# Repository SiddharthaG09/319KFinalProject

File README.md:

# 319KFinalProject

For our final project, we recreated Space Invaders in C, using a custom-designed PCB and an MSPM0G3507 microcontroller. The game integrates hardware components including buttons, a slide potentiometer, and a DAC to control gameplay elements. We designed, printed, and assembled the PCB ourselves, and developed the game logic and graphics from scratch to run on the microcontroller.

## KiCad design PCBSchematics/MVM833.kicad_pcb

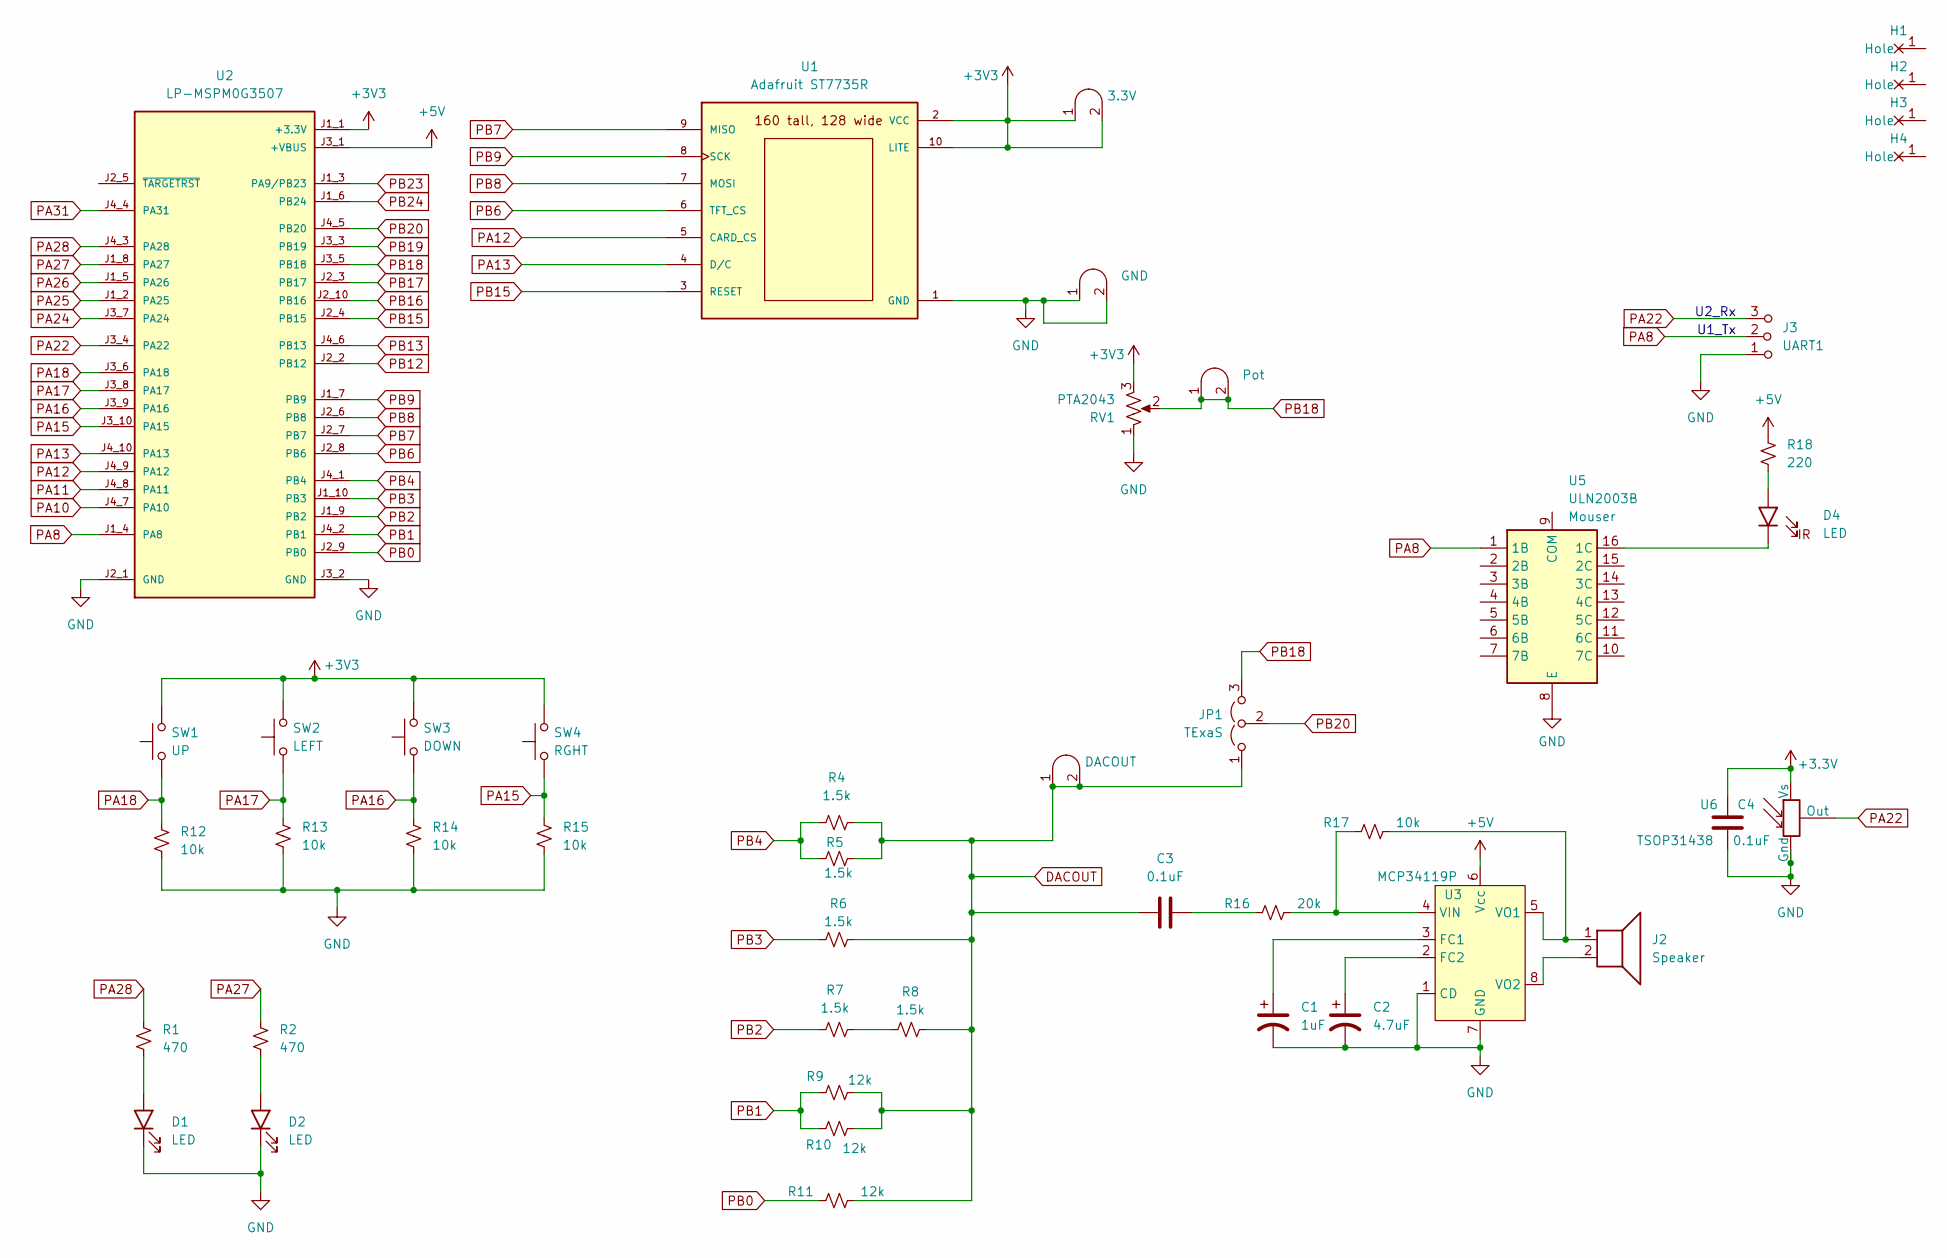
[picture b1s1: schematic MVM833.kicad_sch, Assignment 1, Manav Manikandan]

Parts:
C1: 1uF; CP_Radial_Tantal200mil
C2: 4.7uF; CP_Radial_Tantal200mil
C3, C4: 0.1uF; C_Axial_200mil
D1, D2, D4: LED; LED_D5.0mm
H1, H2, H3, H4: MountingHole_4_40
J2: Speaker; PinHeader_1x02_P2.54mm_Vertical
J3: UART1; PinHeader_1x03_P2.54mm_Vertical
J4: Pot; Testpoint_1x02_P2.54mm
J6: GND; Testpoint_1x02_P2.54mm
J7: DACOUT; Testpoint_1x02_P2.54mm
JP1: TExaS; PinHeader_1x03_P2.54mm_Vertical
R1, R2: 470; R_Axial_DIN0204_L3.6mm_D1.6mm_P7.62mm_Horizontal
R4, R5, R6, R7, R8: 1.5k; R_Axial_DIN0204_L3.6mm_D1.6mm_P7.62mm_Horizontal
R9, R10, R11: 12k; R_Axial_DIN0204_L3.6mm_D1.6mm_P7.62mm_Horizontal
R12, R13, R14, R15, R17: 10k; R_Axial_DIN0204_L3.6mm_D1.6mm_P7.62mm_Horizontal
R16: 20k; R_Axial_DIN0204_L3.6mm_D1.6mm_P7.62mm_Horizontal
R18: 220; R_Axial_DIN0204_L3.6mm_D1.6mm_P7.62mm_Horizontal
RV1: PTA2043; PTA2043pot
SW1: UP; SW_PUSH_6mm
SW2: LEFT; SW_PUSH_6mm
SW3: DOWN; SW_PUSH_6mm
SW4: RGHT; SW_PUSH_6mm
TP1: 3.3V; Testpoint_1x02_P2.54mm
U1: Adafruit ST7735R; adafruit_st7735r
U2: LP-MSPM0G3507; ti_LP_MSPM0G3507
U3: MCP34119P; DIP-8_W7.62mm_LongPads
U5: ULN2003B; DIP-16_W7.62mm
U6: TSOP31438

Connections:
+3.3V: C4.1, U6.2 (Vs)
+3V3: RV1.3, SW1.2, SW2.2, SW3.2, SW4.2, TP1.1 (A), TP1.2 (B), U1.2 (VCC), U1.10 (LITE), U2.J1_1 (+3.3V)
+5V: R18.1, U2.J3_1 (+VBUS), U3.6 (Vcc)
DACOUT: C3.1, J7.1 (A), J7.2 (B), JP1.1 (A), R4.1, R5.1, R6.1, R8.1, R9.1, R10.1, R11.1
GND: C1.2, C2.2, C4.2, D1.1 (K), D2.1 (K), J3.1 (A), J6.1 (A), J6.2 (B), R12.2, R13.2, R14.2, R15.2, RV1.1, U1.1 (GND), U2.J2_1 (GND), U2.J3_2 (GND), U3.1 (CD), U3.7 (GND), U5.8 (E), U6.1 (Gnd)
unnamed: C3.2, R16.2
unnamed: D1.2 (A), R1.2
unnamed: D2.2 (A), R2.2
unnamed: D4.2 (A), R18.2
unnamed: D4.1 (K), U5.16 (1C)
unnamed: R7.1, R8.2
unnamed: C1.1, U3.3 (FC1)
unnamed: C2.1, U3.2 (FC2)
unnamed: R16.1, R17.2, U3.4 (VIN)
unnamed: J2.1, R17.1, U3.5 (VO1)
unnamed: J2.2, U3.8 (VO2)
PA8: J3.2 (B), U2.J1_4 (PA8), U5.1 (1B)
PA10: U2.J4_7 (PA10)
PA11: U2.J4_8 (PA11)
PA12: U1.5 (CARD_CS), U2.J4_9 (PA12)
PA13: U1.4 (D/C), U2.J4_10 (PA13)
PA15: R15.1, SW4.1, U2.J3_10 (PA15)
PA16: R14.1, SW3.1, U2.J3_9 (PA16)
PA17: R13.1, SW2.1, U2.J3_8 (PA17)
PA18: R12.1, SW1.1, U2.J3_6 (PA18)
PA22: J3.3 (C), U2.J3_4 (PA22), U6.3 (Out)
PA24: U2.J3_7 (PA24)
PA25: U2.J1_2 (PA25)
PA26: U2.J1_5 (PA26)
PA27: R2.1, U2.J1_8 (PA27)
PA28: R1.1, U2.J4_3 (PA28)
PA31: U2.J4_4 (PA31)
PB0: R11.2, U2.J2_9 (PB0)
PB1: R9.2, R10.2, U2.J4_2 (PB1)
PB2: R7.2, U2.J1_9 (PB2)
PB3: R6.2, U2.J1_10 (PB3)
PB4: R4.2, R5.2, U2.J4_1 (PB4)
PB6: U1.6 (TFT_CS), U2.J2_8 (PB6)
PB7: U1.9 (MISO), U2.J2_7 (PB7)
PB8: U1.7 (MOSI), U2.J2_6 (PB8)
PB9: U1.8 (SCK), U2.J1_7 (PB9)
PB12: U2.J2_2 (PB12)
PB13: U2.J4_6 (PB13)
PB15: U1.3 (RESET), U2.J2_4 (PB15)
PB16: U2.J2_10 (PB16)
PB17: U2.J2_3 (PB17)
PB18: J4.1 (A), J4.2 (B), JP1.3 (B), RV1.2, U2.J3_5 (PB18)
PB19: U2.J3_3 (PB19)
PB20: JP1.2 (C), U2.J4_5 (PB20)
PB23: U2.J1_3 (PA9/PB23)
PB24: U2.J1_6 (PB24)

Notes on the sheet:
U2_Rx
U1_Tx

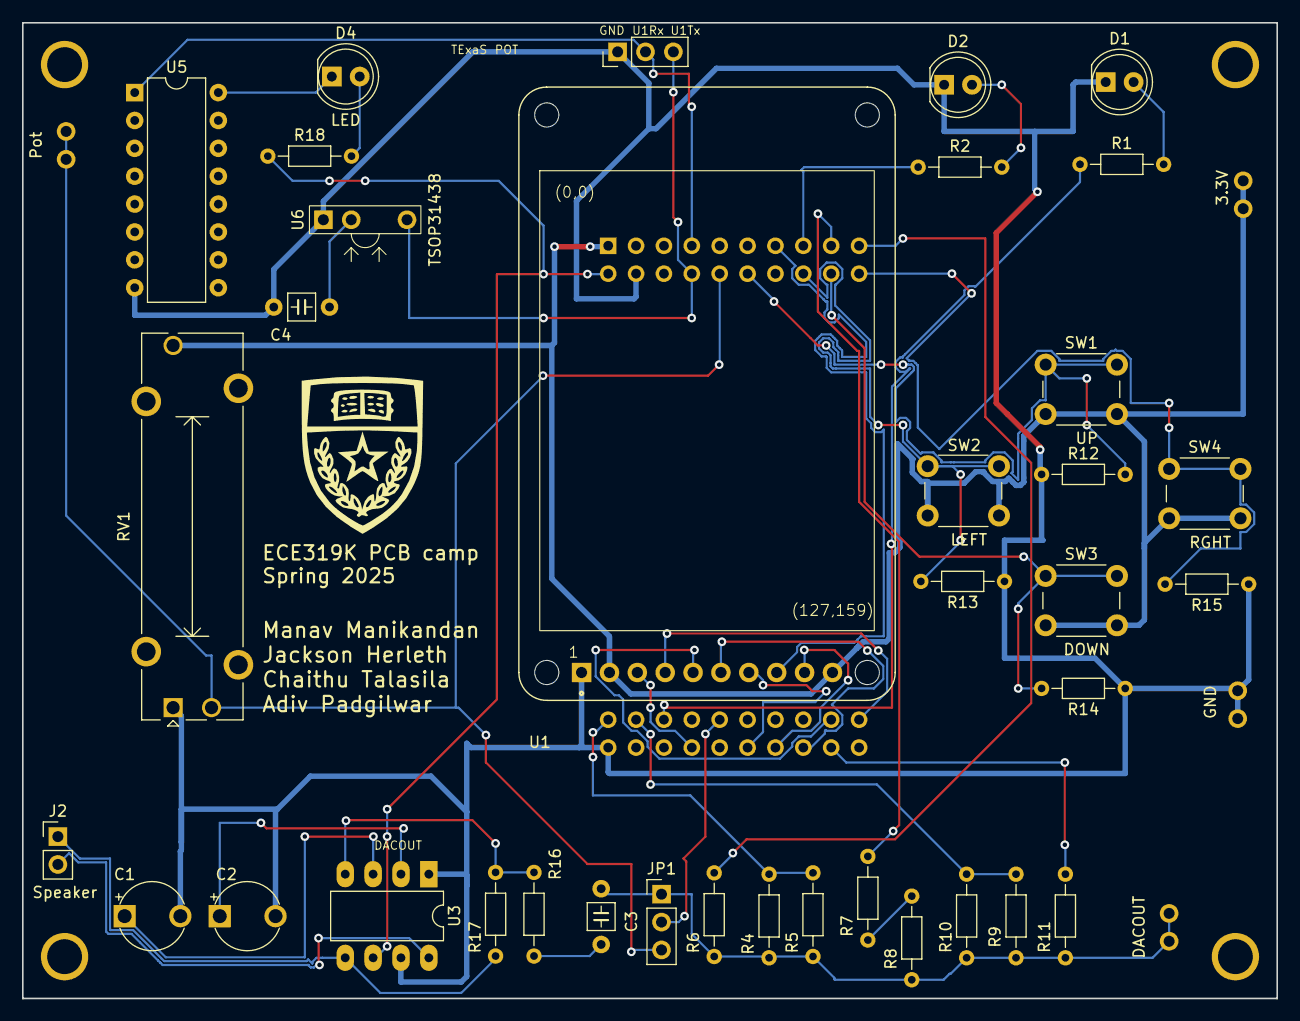
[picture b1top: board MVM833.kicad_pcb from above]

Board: 2 copper layers, 114.3 x 88.9 mm, 45 parts (1 on the bottom side), 38 nets.

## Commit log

2025-04-28 Added Project Folder
2025-04-28 Uploaded PCB
